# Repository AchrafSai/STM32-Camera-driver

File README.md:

# STM32 Camera Driver PCB

This project is a custom-designed Printed Circuit Board (PCB) that integrates an STM32H7 microcontroller, a camera module, a display, five buttons, and multiple communication ports.

## Features
The key features of this project are:

STM32H7 Microcontroller: The STM32H7 is a powerful 32-bit microcontroller with a dual-core ARM Cortex-M7 and Cortex-M4 processor, capable of running at up to 480 MHz. It offers a wide range of peripherals and connectivity options, making it ideal for embedded systems applications.

Camera Module: The camera module used in this project is a high-resolution OV5640 sensor that captures 5-megapixel still images and 720p video at 60 frames per second.

Display: The display used in this project is a 1.8-inch TFT LCD screen with a resolution of 320x240 pixels. It provides a clear and bright display for viewing images and video captured by the camera.

Five Buttons: The board includes five buttons for user input, allowing users to control the camera and interact with the user interface displayed on the screen.

Communication Ports: The board includes multiple communication ports, including USB, UART, SPI, and I2C, providing flexibility for communicating with other devices and systems.

## Repository Contents
This repository contains the design files for the PCB, including the schematic, PCB layout, and bill of materials. The KiCad project files are provided, as well as PDFs of the schematic and PCB layout for easy viewing.

## Getting Started
To use this PCB, you will need to assemble and program it. The bill of materials provides a list of components needed, and the KiCad project files can be used to generate the Gerber files needed to manufacture the PCB.

Once the PCB is assembled, you can use the provided example code to get started. The code includes basic functionality for capturing images and video, displaying them on the screen, and interacting with the user through the buttons.

## License
This project is released under the MIT License, meaning that you are free to use, modify, and distribute the code and design files for both personal and commercial use. However, please note that the camera module used in this project may be subject to additional licensing restrictions.

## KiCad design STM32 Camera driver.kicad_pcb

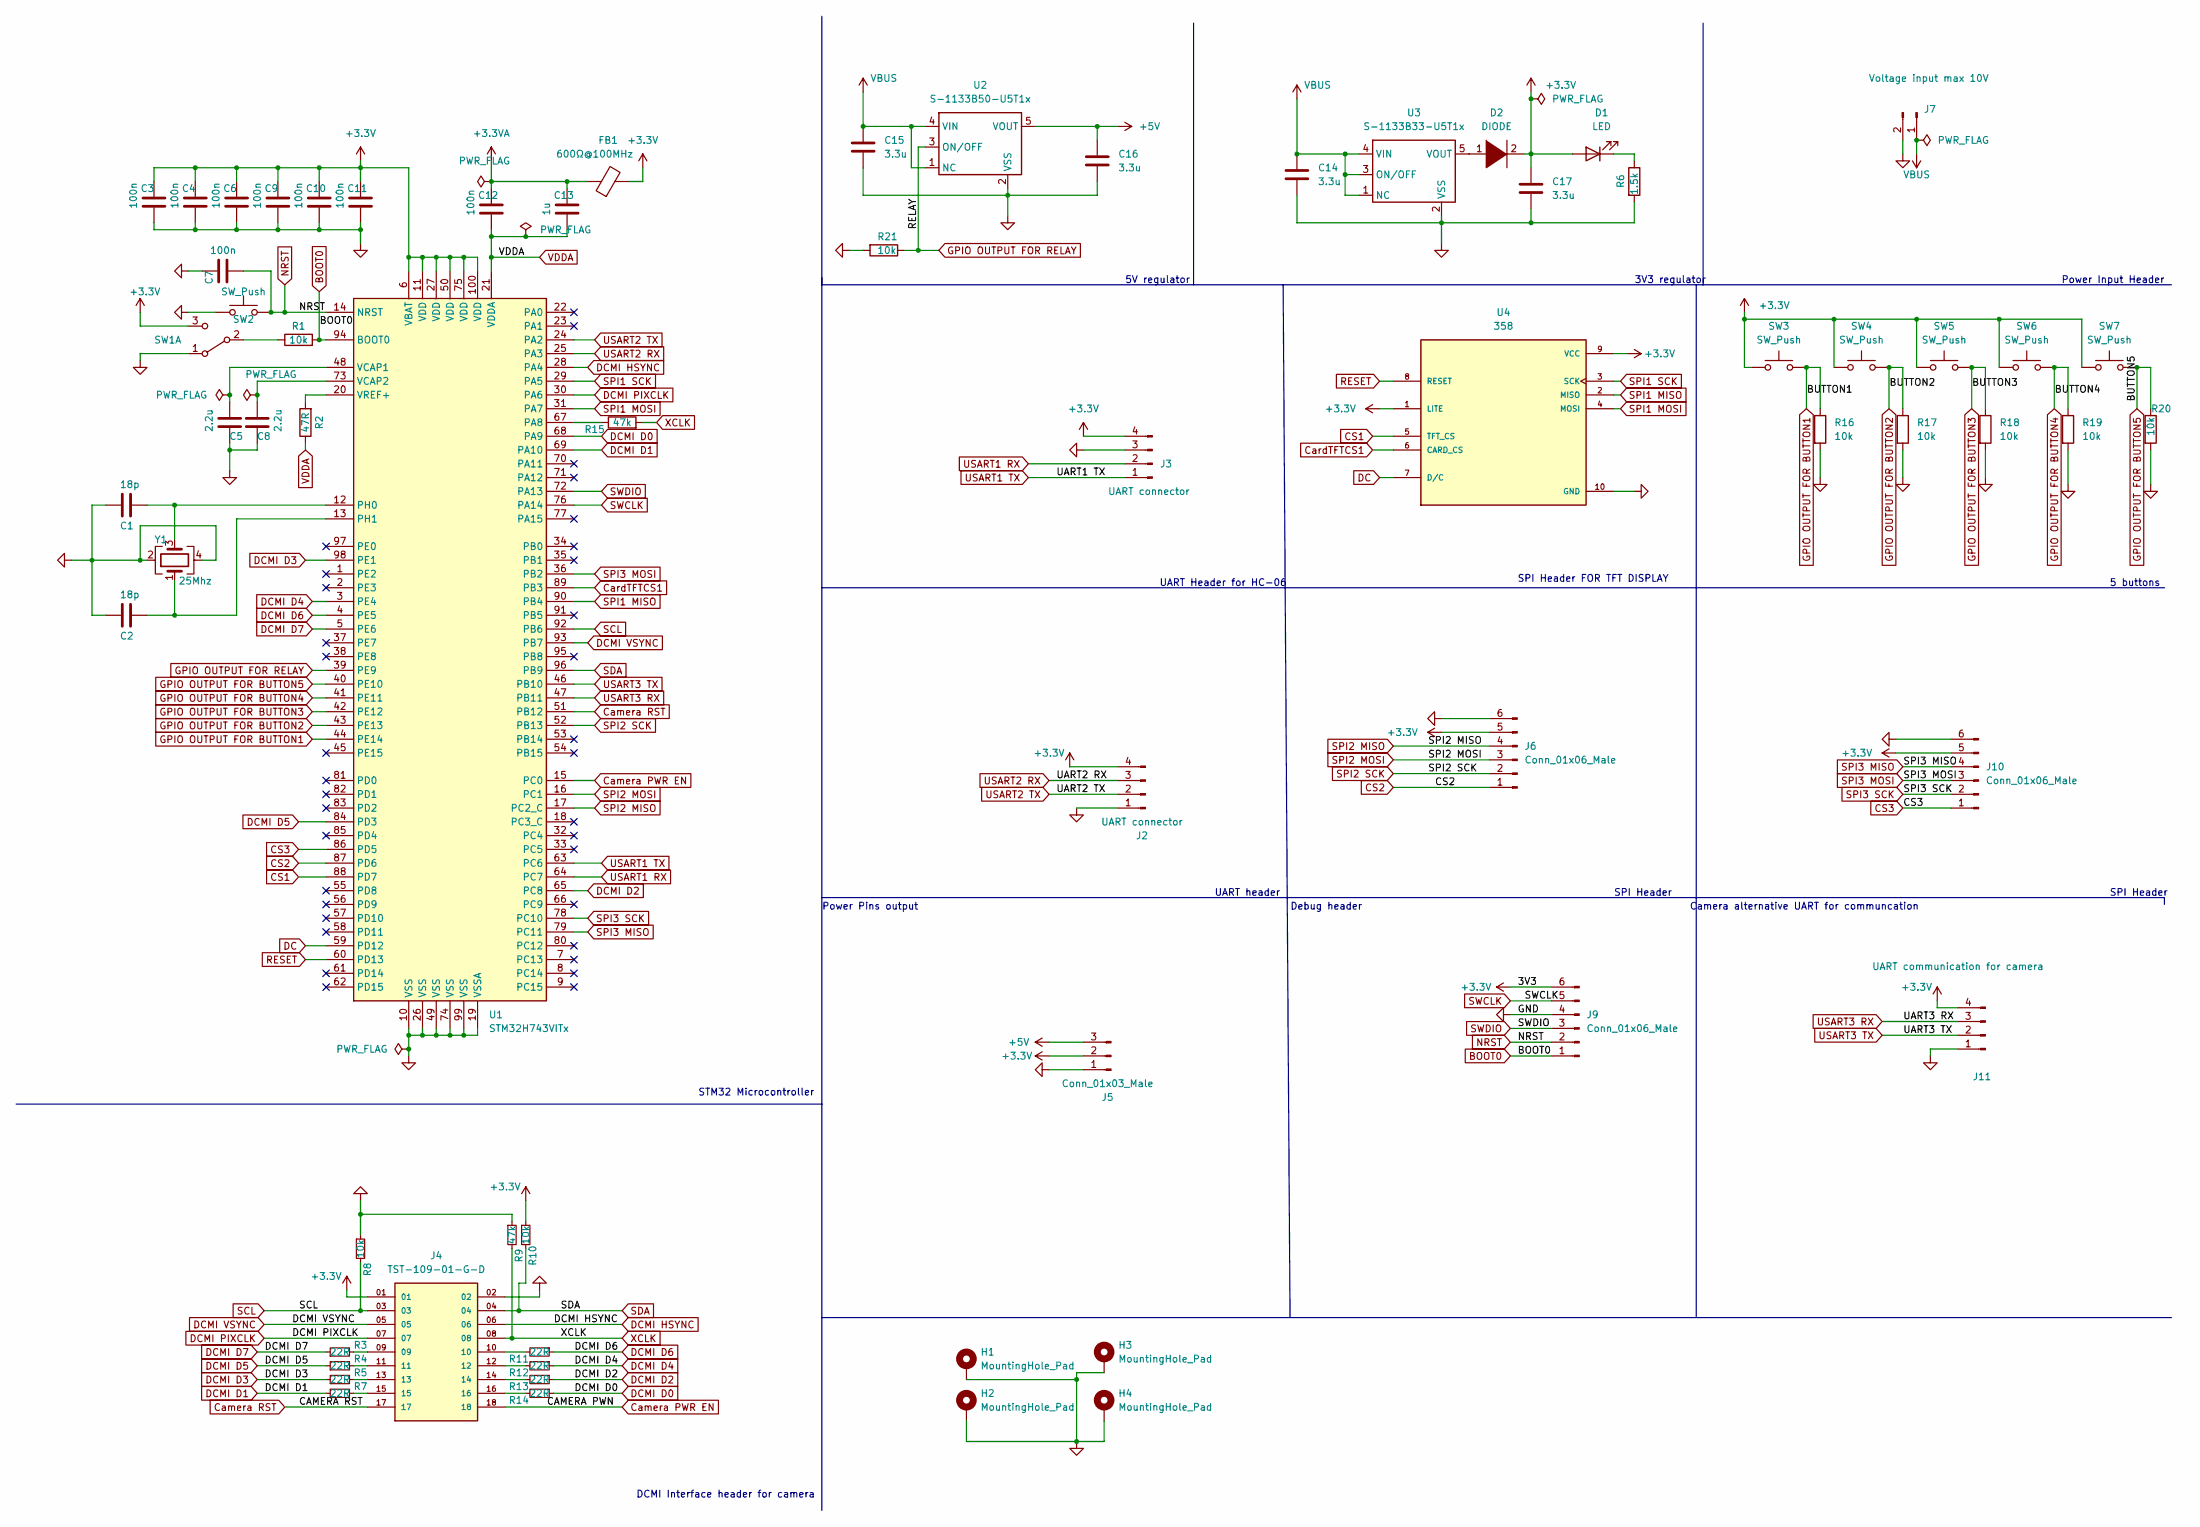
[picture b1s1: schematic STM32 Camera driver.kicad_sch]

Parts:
C1, C2: 18p; C_0402_1005Metric_Pad0.74x0.62mm_HandSolder
C3, C4, C6, C7, C9, C10, C11, C12: 100n; C_0402_1005Metric_Pad0.74x0.62mm_HandSolder
C5, C8: 2.2u; C_0402_1005Metric_Pad0.74x0.62mm_HandSolder
C13: 1u; C_0402_1005Metric_Pad0.74x0.62mm_HandSolder
C14, C15, C16, C17: 3.3u; C_0402_1005Metric_Pad0.74x0.62mm_HandSolder
D1: LED; LED_0805_2012Metric_Pad1.15x1.40mm_HandSolder
D2: DIODE; D_SOD-123F
FB1: 600Ω@100MHz; L_0402_1005Metric_Pad0.77x0.64mm_HandSolder
H1, H2, H3, H4: MountingHole_Pad; MountingHole_2.7mm_M2.5_ISO14580_Pad
J2, J3: UART connector; JST_EH_B4B-EH-A_1x04_P2.50mm_Vertical
J4: TST-109-01-G-D; SAMTEC_TST-109-01-G-D; PARTREV R
J5: Conn_01x03_Male; JST_EH_B3B-EH-A_1x03_P2.50mm_Vertical
J6, J9, J10: Conn_01x06_Male; JST_EH_B6B-EH-A_1x06_P2.50mm_Vertical
J7: Voltage input max 10V; PhoenixContact_MCV_1,5_2-G-5.08_1x02_P5.08mm_Vertical
J11: UART communication for camera; JST_EH_B4B-EH-A_1x04_P2.50mm_Vertical
R1, R8, R10, R16, R17, R18, R19, R20, R21: 10k; R_0402_1005Metric_Pad0.72x0.64mm_HandSolder
R2: 47R; R_0402_1005Metric_Pad0.72x0.64mm_HandSolder
R3, R4, R5, R7, R11, R12, R13, R14: 22R; R_0402_1005Metric_Pad0.72x0.64mm_HandSolder
R6: 1.5k; R_0402_1005Metric_Pad0.72x0.64mm_HandSolder
R9, R15: 47k; R_0402_1005Metric_Pad0.72x0.64mm_HandSolder
SW1: SW_DPDT_x2; SW_CuK_JS202011AQN_DPDT_Angled
SW2: SW_Push; SW_PUSH_6mm
SW3, SW4, SW5, SW6, SW7: SW_Push; SW_PB300STQ_copy
U1: STM32H743VITx; LQFP-100_14x14mm_P0.5mm
U2: S-1133B50-U5T1x; SOT-89-5_Handsoldering
U3: S-1133B33-U5T1x; SOT-89-5_Handsoldering
U4: 358; MODULE_358; PARTREV 2021-12-09
Y1: 25Mhz; Crystal_SMD_3225-4Pin_3.2x2.5mm_HandSoldering

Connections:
+3.3V: C3.1, C4.1, C6.1, C9.1, C10.1, C11.1, C17.1, D1.2 (A), D2.2 (A), FB1.2, J2.4, J3.4, J4.01, J5.2, J6.5, J9.6, J10.5, J11.4, R10.1, SW1.3 (C), SW3.1, SW4.1, SW5.1, SW6.1, SW7.1, U1.6 (VBAT), U1.11 (VDD), U1.27 (VDD), U1.50 (VDD), U1.75 (VDD), U1.100 (VDD), U4.1 (LITE), U4.9 (VCC); also elsewhere on the board
+3.3VA: C12.1, C13.1, FB1.1
+5V: C16.1, J5.3, U2.5 (VOUT)
BOOT0: J9.1, R1.2, U1.94 (BOOT0)
CS1: U1.88 (PD7), U4.5 (TFT_CS)
CS2: J6.1, U1.87 (PD6)
CS3: J10.1, U1.86 (PD5)
Camera PWR EN: J4.18, U1.15 (PC0)
Camera RST: J4.17, U1.51 (PB12)
CardTFTCS1: U1.89 (PB3), U4.6 (CARD_CS)
DC: U1.59 (PD12), U4.7 (D/C)
DCMI D0: R14.1, U1.68 (PA9)
DCMI D1: R7.1, U1.69 (PA10)
DCMI D2: R13.1, U1.65 (PC8)
DCMI D3: R5.1, U1.98 (PE1)
DCMI D4: R12.1, U1.3 (PE4)
DCMI D5: R4.1, U1.84 (PD3)
DCMI D6: R11.1, U1.4 (PE5)
DCMI D7: R3.1, U1.5 (PE6)
DCMI HSYNC: J4.06, U1.28 (PA4)
DCMI PIXCLK: J4.07, U1.30 (PA6)
DCMI VSYNC: J4.05, U1.93 (PB7)
GND: C1.2, C2.2, C3.2, C4.2, C5.1, C6.2, C7.1, C8.1, C9.2, C10.2, C11.2, C14.1, C15.1, C16.2, C17.2, H1.1, H2.1, H3.1, H4.1, J2.1, J3.3, J4.02, J5.1, J6.6, J7.2, J9.4, J10.6, J11.1, R6.2, R8.1, R9.1, R16.2, R17.2, R18.2, R19.2, R20.2, R21.2, SW1.1 (A), SW2.1, U1.10 (VSS), U1.19 (VSSA), U1.26 (VSS), U1.49 (VSS), U1.74 (VSS), U1.99 (VSS), U2.2 (VSS), U3.2 (VSS), U4.10 (GND), Y1.2, Y1.4; also elsewhere on the board
GPIO OUTPUT FOR BUTTON1: R16.1, SW3.2, U1.44 (PE14)
GPIO OUTPUT FOR BUTTON2: R17.1, SW4.2, U1.43 (PE13)
GPIO OUTPUT FOR BUTTON3: R18.1, SW5.2, U1.42 (PE12)
GPIO OUTPUT FOR BUTTON4: R19.1, SW6.2, U1.41 (PE11)
GPIO OUTPUT FOR BUTTON5: R20.1, SW7.2, U1.40 (PE10)
GPIO OUTPUT FOR RELAY: R21.1, U1.39 (PE9), U2.3 (ON/OFF)
NRST: C7.2, J9.2, SW2.2, U1.14 (NRST); also elsewhere on the board
unnamed: C1.1, U1.12 (PH0), Y1.3
unnamed: C2.1, U1.13 (PH1), Y1.1
unnamed: C5.2, U1.48 (VCAP1)
unnamed: C8.2, U1.73 (VCAP2)
unnamed: D1.1 (K), R6.1
unnamed: D2.1 (K), U3.5 (VOUT)
unnamed: J4.09, R3.2
unnamed: J4.10, R11.2
unnamed: J4.11, R4.2
unnamed: J4.12, R12.2
unnamed: J4.13, R5.2
unnamed: J4.14, R13.2
unnamed: J4.15, R7.2
unnamed: J4.16, R14.2
unnamed 44: R1.1, SW1.2 (B); also elsewhere on the board
unnamed: R2.2, U1.20 (VREF+)
unnamed: R15.1, U1.67 (PA8)
RESET: U1.60 (PD13), U4.8 (RESET)
SCL: J4.03, R8.2, U1.92 (PB6)
SDA: J4.04, R10.2, U1.96 (PB9)
SPI1 MISO: U1.90 (PB4), U4.2 (MISO)
SPI1 MOSI: U1.31 (PA7), U4.4 (MOSI)
SPI1 SCK: U1.29 (PA5), U4.3 (SCK)
SPI2 MISO: J6.4, U1.17 (PC2_C)
SPI2 MOSI: J6.3, U1.16 (PC1)
SPI2 SCK: J6.2, U1.52 (PB13)
SPI3 MISO: J10.4, U1.79 (PC11)
SPI3 MOSI: J10.3, U1.36 (PB2)
SPI3 SCK: J10.2, U1.78 (PC10)
SWCLK: J9.5, U1.76 (PA14)
SWDIO: J9.3, U1.72 (PA13)
USART1 RX: J3.2, U1.64 (PC7)
USART1 TX: J3.1, U1.63 (PC6)
USART2 RX: J2.3, U1.25 (PA3)
USART2 TX: J2.2, U1.24 (PA2)
USART3 RX: J11.3, U1.47 (PB11)
USART3 TX: J11.2, U1.46 (PB10)
VBUS: C14.2, C15.2, J7.1, U2.1 (NC), U2.4 (VIN), U3.1 (NC), U3.3 (ON/OFF), U3.4 (VIN)
VDDA: C12.2, C13.2, R2.1, U1.21 (VDDA)
XCLK: J4.08, R9.2, R15.2

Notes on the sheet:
Debug header
Power Pins output
UART header
5V regulator
3V3 regulator
UART Header for HC-06
Camera alternative UART for communcation
5 buttons
STM32 Microcontroller
SPI Header
SPI Header FOR TFT DISPLAY
Power Input Header
DCMI Interface header for camera

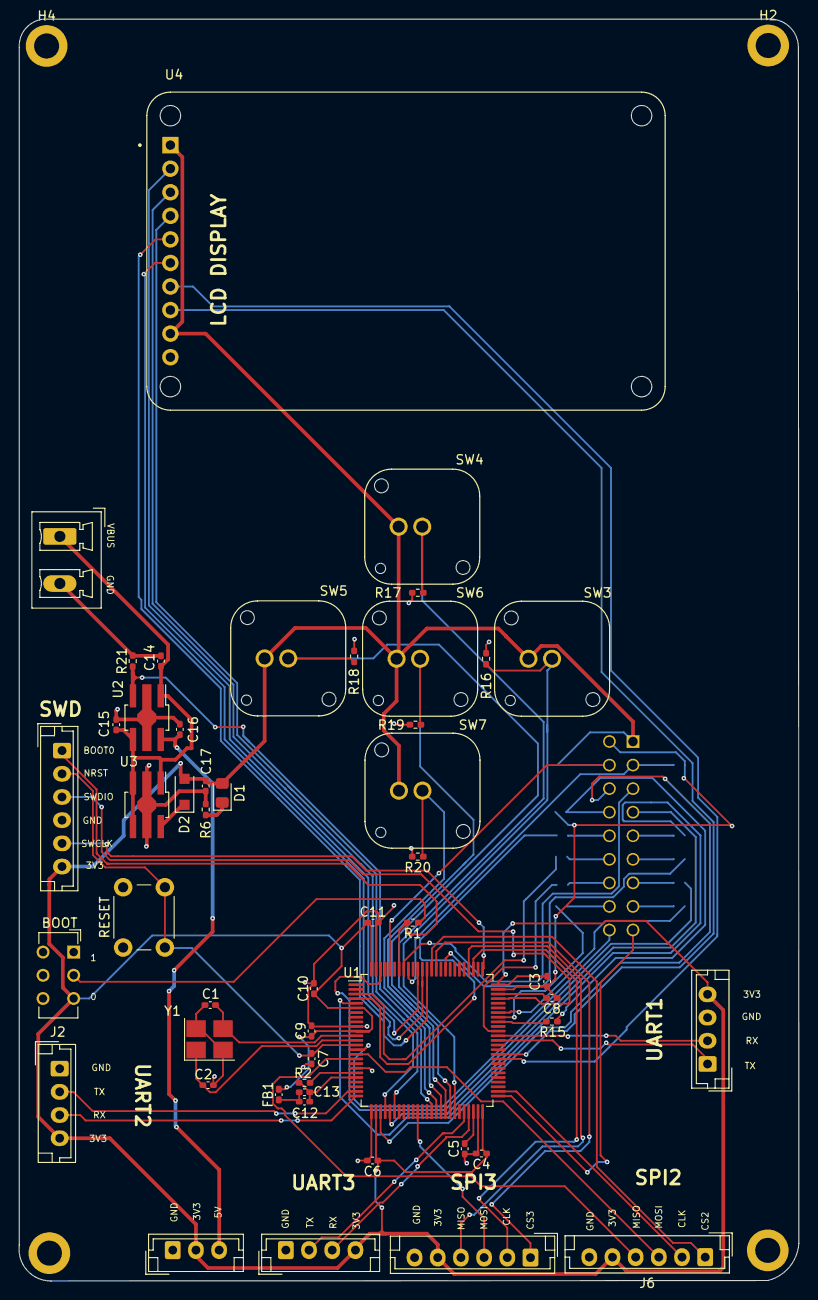
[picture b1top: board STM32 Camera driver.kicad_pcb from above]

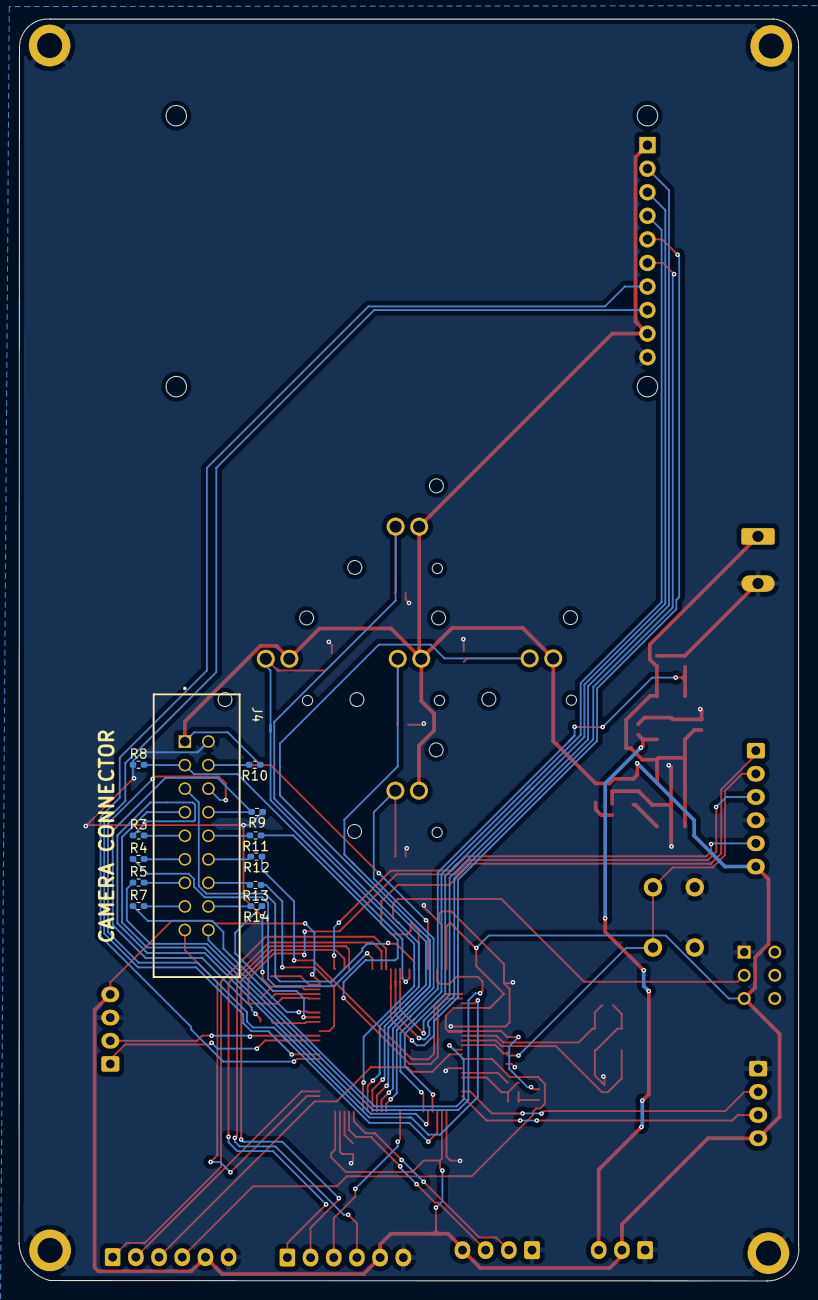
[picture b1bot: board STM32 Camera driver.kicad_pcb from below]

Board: 2 copper layers, 84.1 x 136.1 mm, 66 parts (12 on the bottom side), 70 nets.

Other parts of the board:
BOOT: SW_DPDT_x2; SW_CuK_JS202011AQN_DPDT_Angled
RESET: SW_Push; SW_PUSH_6mm

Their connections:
+3.3V: BOOT.3 (C); also elsewhere on the board
GND: BOOT.1 (A), RESET.1; also elsewhere on the board
NRST: RESET.2; also elsewhere on the board
unnamed 44: BOOT.2 (B); also elsewhere on the board

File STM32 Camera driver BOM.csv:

Source:,/home/achraf/Documents/KiCad/STM32 Camera driver/STM32 Camera driver.kicad_sch,,,,,
Date:,"02,15,2023",,,,,
Tool:,Eeschema 6.0.10-86aedd382b~118~ubuntu20.04.1,,,,,
Generator:,/usr/share/kicad/plugins/bom_csv_grouped_by_value_with_fp.py,,,,,
Component Count:,66,,,,,
Ref,Qnty,Value,Cmp name,Footprint,Description,Vendor
"C1, C2, ",2,18p,C,Capacitor_SMD:C_0402_1005Metric_Pad0.74x0.62mm_HandSolder,Unpolarized capacitor,
"C3, C4, C6, C7, C9, C10, C11, C12, ",8,100n,C,Capacitor_SMD:C_0402_1005Metric_Pad0.74x0.62mm_HandSolder,Unpolarized capacitor,
"C5, C8, ",2,2.2u,C,Capacitor_SMD:C_0402_1005Metric_Pad0.74x0.62mm_HandSolder,Unpolarized capacitor,
"C13, ",1,1u,C,Capacitor_SMD:C_0402_1005Metric_Pad0.74x0.62mm_HandSolder,Unpolarized capacitor,
"C14, C15, C16, C17, ",4,3.3u,C,Capacitor_SMD:C_0402_1005Metric_Pad0.74x0.62mm_HandSolder,Unpolarized capacitor,
"D1, ",1,LED,LED,LED_SMD:LED_0805_2012Metric_Pad1.15x1.40mm_HandSolder,Light emitting diode,
"D2, ",1,DIODE,DIODE,Diode_SMD:D_SOD-123F,,https://www.lcsc.com/product-detail/Switching-span-style-bac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
"FB1, ",1,600Ω@100MHz,FerriteBead,Inductor_SMD:L_0402_1005Metric_Pad0.77x0.64mm_HandSolder,Ferrite bead,https://www.lcsc.com/product-detail/Ferrite-Beads_Murata-Ele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
"H1, H2, H3, H4, ",4,MountingHole_Pad,MountingHole_Pad,MountingHole:MountingHole_2.7mm_M2.5_ISO14580_Pad,Mounting Hole with connection,
"J2, J3, ",2,UART connector,Conn_01x04_Male,Connector_JST:JST_EH_B4B-EH-A_1x04_P2.50mm_Vertical,"Generic connector, single row, 01x04, script generated (kicad-library-utils/schlib/autogen/connector/)",
"J4, ",1,TST-109-01-G-D,TST-109-01-G-D,Library:SAMTEC_TST-109-01-G-D,,
"J5, ",1,Conn_01x03_Male,Conn_01x03_Male,Connector_JST:JST_EH_B3B-EH-A_1x03_P2.50mm_Vertical,"Generic connector, single row, 01x03, script generated (kicad-library-utils/schlib/autogen/connector/)",
"J6, J9, J10, ",3,Conn_01x06_Male,Conn_01x06_Male,Connector_JST:JST_EH_B6B-EH-A_1x06_P2.50mm_Vertical,"Generic connector, single row, 01x06, script generated (kicad-library-utils/schlib/autogen/connector/)",
"J7, ",1,Voltage input max 10V,Conn_01x02_Male,"Connector_Phoenix_MC_HighVoltage:PhoenixContact_MCV_1,5_2-G-5.08_1x02_P5.08mm_Vertical","Generic connector, single row, 01x02, script generated (kicad-library-utils/schlib/autogen/connector/)",
"J11, ",1,UART communication for camera ,Conn_01x04_Male,Connector_JST:JST_EH_B4B-EH-A_1x04_P2.50mm_Vertical,"Generic connector, single row, 01x04, script generated (kicad-library-utils/schlib/autogen/connector/)",
"R1, R8, R10, R16, R17, R18, R19, R20, R21, ",9,10k,R,Resistor_SMD:R_0402_1005Metric_Pad0.72x0.64mm_HandSolder,Resistor,
"R2, ",1,47R,R,Resistor_SMD:R_0402_1005Metric_Pad0.72x0.64mm_HandSolder,Resistor,
"R3, R4, R5, R7, R11, R12, R13, R14, ",8,22R,R_Small,Resistor_SMD:R_0402_1005Metric_Pad0.72x0.64mm_HandSolder,"Resistor, small symbol",
"R6, ",1,1.5k,R,Resistor_SMD:R_0402_1005Metric_Pad0.72x0.64mm_HandSolder,Resistor,
"R9, R15, ",2,47k,R,Resistor_SMD:R_0402_1005Metric_Pad0.72x0.64mm_HandSolder,Resistor,
"SW1, ",1,SW_DPDT_x2,SW_DPDT_x2,Button_Switch_THT:SW_CuK_JS202011AQN_DPDT_Angled,"Switch, dual pole double throw, separate symbols",
"SW2, ",1,SW_Push,SW_Push,Button_Switch_THT:SW_PUSH_6mm,"Push button switch, generic, two pins",
"SW3, SW4, SW5, SW6, SW7, ",5,SW_Push,SW_Push,Library:SW_PB300STQ_copy,"Push button switch, generic, two pins",https://www.e-switch.com/product-catalog/pb300-series-long-t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
"U1, ",1,STM32H743VITx,STM32H743VITx,Package_QFP:LQFP-100_14x14mm_P0.5mm,"ARM Cortex-M7 MCU, 2048KB flash, 864KB RAM, 400MHz, 1.7-3.6V, 82 GPIO, LQFP-100",
"U2, ",1,S-1133B50-U5T1x,S-1133_Series_1,Library:SOT-89-5_Handsoldering,,
"U3, ",1,S-1133B33-U5T1x,S-1133_Series_1,Library:SOT-89-5_Handsoldering,,
"U4, ",1,358,358,Library:MODULE_358,,
"Y1, ",1,25Mhz,Crystal_GND24,Crystal:Crystal_SMD_3225-4Pin_3.2x2.5mm_HandSoldering,"Four pin crystal, GND on pins 2 and 4",https://www.lcsc.com/product-detail/Oscillators_TAITIEN-Elec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
